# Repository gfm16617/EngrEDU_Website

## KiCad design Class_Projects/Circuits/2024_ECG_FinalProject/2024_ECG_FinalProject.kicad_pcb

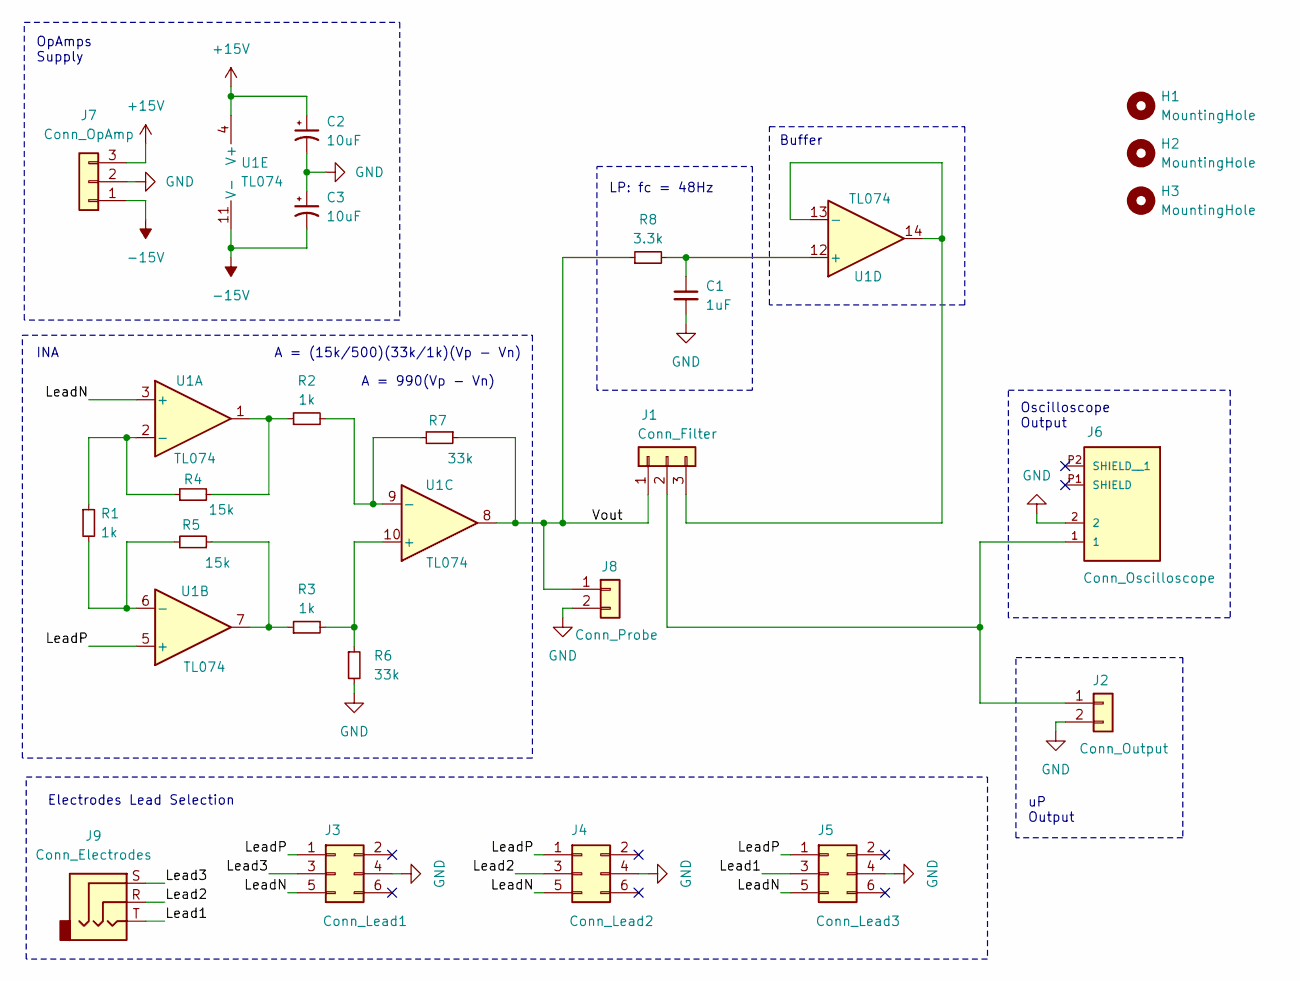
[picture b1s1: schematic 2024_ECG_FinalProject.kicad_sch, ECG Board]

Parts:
C1: 1uF; C_Disc_D5.0mm_W2.5mm_P5.00mm
C2, C3: 10uF; CP_Radial_D5.0mm_P2.50mm
H1, H2, H3: MountingHole; MountingHole_3.2mm_M3_Pad
J1: Conn_Filter; PinHeader_1x03_P2.54mm_Vertical
J2: Conn_Output; PinHeader_1x02_P2.54mm_Vertical
J3: Conn_Lead1; PinHeader_2x03_P2.54mm_Vertical
J4: Conn_Lead2; PinHeader_2x03_P2.54mm_Vertical
J5: Conn_Lead3; PinHeader_2x03_P2.54mm_Vertical
J6: Conn_Oscilloscope; BNC_RightAngle_50ohm
J7: Conn_OpAmp; PinHeader_1x03_P2.54mm_Vertical
J8: Conn_Probe; PinHeader_1x02_P2.54mm_Vertical
J9: Conn_Electrodes; AudioJack_CUI_3mm5
R1, R2, R3: 1k; R_Axial_DIN0207_L6.3mm_D2.5mm_P10.16mm_Horizontal
R4, R5: 15k; R_Axial_DIN0207_L6.3mm_D2.5mm_P10.16mm_Horizontal
R6, R7: 33k; R_Axial_DIN0207_L6.3mm_D2.5mm_P10.16mm_Horizontal
R8: 3.3k; R_Axial_DIN0207_L6.3mm_D2.5mm_P10.16mm_Horizontal
U1: TL074; CERDIP-14_W7.62mm_SideBrazed_LongPads_Socket

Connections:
+15V: C2.1, J7.3, U1.4 (V+)
-15V: C3.2, J7.1, U1.11 (V-)
/Lead1: J5.3, J9.T
/Lead2: J4.3, J9.R
/Lead3: J3.3, J9.S
/LeadN: J3.5, J4.5, J5.5, U1.3 (+)
/LeadP: J3.1, J4.1, J5.1, U1.5 (+)
/Vout: J1.1, J8.1, R7.1, R8.1, U1.8
GND: C1.2, C2.2, C3.1, J2.2, J3.4, J4.4, J5.4, J6.2, J7.2, J8.2, R6.2
unnamed: J1.2, J2.1, J6.1
unnamed: J1.3, U1.13 (-), U1.14
unnamed: R2.1, R4.2, U1.1
unnamed: R3.1, R5.2, U1.7
unnamed: R1.1, R4.1, U1.2 (-)
unnamed: R1.2, R5.1, U1.6 (-)
unnamed: R3.2, R6.1, U1.10 (+)
unnamed: R2.2, R7.2, U1.9 (-)
unnamed: C1.1, R8.2, U1.12 (+)

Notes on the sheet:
INA
Buffer
A = 990(Vp - Vn)
OpAmps Supply
Oscilloscope Output
A = (15k/500)(33k/1k)(Vp - Vn)
uP Output
Electrodes Lead Selection
LP: fc = 48Hz

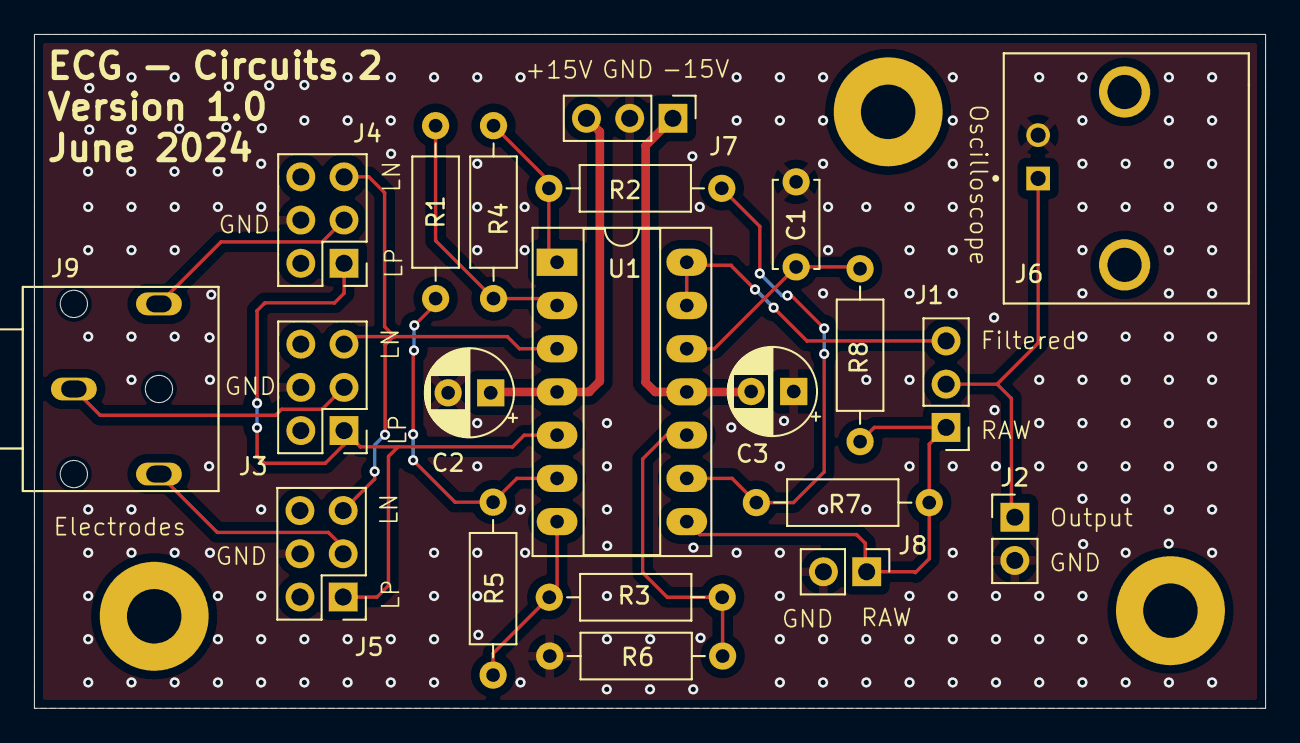
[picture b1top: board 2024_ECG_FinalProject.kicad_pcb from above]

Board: 2 copper layers, 72.3 x 39.6 mm, 24 parts (0 on the bottom side), 18 nets.

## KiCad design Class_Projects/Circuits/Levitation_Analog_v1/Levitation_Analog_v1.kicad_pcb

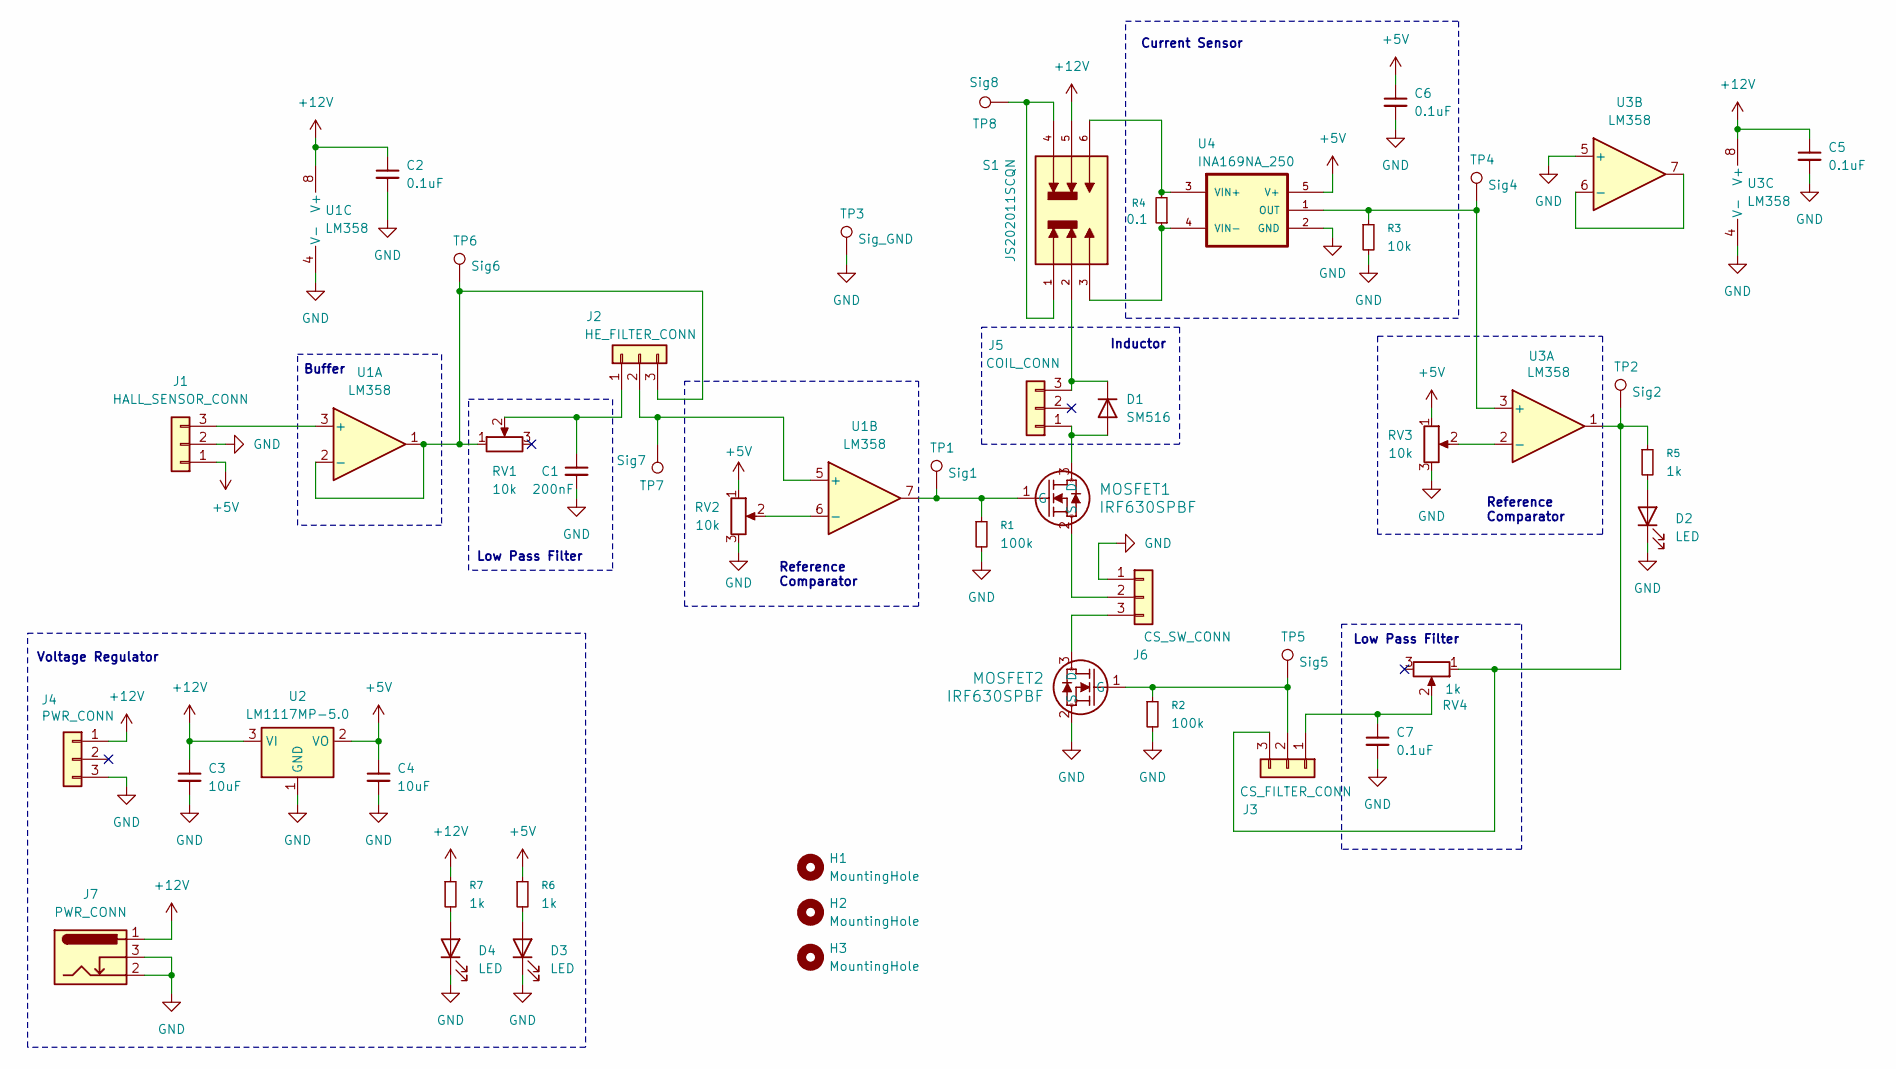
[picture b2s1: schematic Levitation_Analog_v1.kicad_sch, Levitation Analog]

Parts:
C1: 200nF; C_1206_3216Metric_Pad1.33x1.80mm_HandSolder; Mfr. # 12065C204KAT4A
C2, C5, C6, C7: 0.1uF; C_1206_3216Metric_Pad1.33x1.80mm_HandSolder; Mfr. # KAM31NR72A104KU
C3, C4: 10uF; C_1206_3216Metric_Pad1.33x1.80mm_HandSolder; Mfr. # GXT31CR6YA106KE01L
D1: SM516; D_MELF; Mfr. # SM516
D2, D3, D4: LED; LED_1206_3216Metric; Mfr. # HSMG-C150
H1, H2, H3: MountingHole; MountingHole_3.2mm_M3_Pad
J1: HALL_SENSOR_CONN; JST_XA_B03B-XASK-1_1x03_P2.50mm_Vertical
J2: HE_FILTER_CONN; PinHeader_1x03_P2.54mm_Vertical
J3: CS_FILTER_CONN; PinHeader_1x03_P2.54mm_Vertical
J4: PWR_CONN; JST_XA_B03B-XASK-1_1x03_P2.50mm_Vertical
J5: COIL_CONN; JST_XA_B03B-XASK-1_1x03_P2.50mm_Vertical
J6: CS_SW_CONN; PinHeader_1x03_P2.54mm_Vertical
J7: PWR_CONN; BarrelJack_Horizontal
MOSFET1, MOSFET2: IRF630SPBF; TO-263AB_HIGHVOLTAGE-M; Mfr. # IRF630SPBF
R1, R2: 100k; R_1206_3216Metric_Pad1.30x1.75mm_HandSolder; Mfr. # RVCU1206FT100K
R3: 10k; R_1206_3216Metric_Pad1.30x1.75mm_HandSolder; Mfr. # SFR18EZPJ103
R4: 0.1; R_1206_3216Metric_Pad1.30x1.75mm_HandSolder; Mfr. # TLMQ2BDR10FTD
R5, R6, R7: 1k; R_1206_3216Metric_Pad1.30x1.75mm_HandSolder; Mfr. # RK73H2BLTD1001F
RV1, RV2, RV3: 10k; Potentiometer_Alps_RK09K_Single_Vertical
RV4: 1k; Potentiometer_Alps_RK09K_Single_Vertical
S1: JS202011SCQN; SW_JS202011SCQN; PARTREV 26 May 22
TP1: Sig1; TestPoint_Loop_D2.50mm_Drill1.0mm
TP2: Sig2; TestPoint_Loop_D2.50mm_Drill1.0mm
TP3: Sig_GND; TestPoint_Loop_D2.50mm_Drill1.0mm
TP4: Sig4; TestPoint_Loop_D2.50mm_Drill1.0mm
TP5: Sig5; TestPoint_Loop_D2.50mm_Drill1.0mm
TP6: Sig6; TestPoint_Loop_D2.50mm_Drill1.0mm
TP7: Sig7; TestPoint_Loop_D2.50mm_Drill1.0mm
TP8: Sig8; TestPoint_Loop_D2.50mm_Drill1.0mm
U1, U3: LM358; SOP-8_3.76x4.96mm_P1.27mm; Mfr. # LM358F-GE2
U2: LM1117MP-5.0; SOT-223-3_TabPin2; Mfr. # LM1117MPX-50NOPB
U4: INA169NA_250; SOT95P280X145-5N; Mfr. # INA169NA/3K

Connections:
+5V: C4.1, C6.1, J1.1, R6.1, RV2.1, RV3.1, U2.2 (VO), U4.5 (V+)
+12V: C2.1, C3.1, C5.1, J4.1, J7.1, R7.1, S1.5, U1.8 (V+), U2.3 (VI), U3.8 (V+)
GND: C1.2, C2.2, C3.2, C4.2, C5.2, C6.2, C7.2, D2.1 (K), D3.1 (K), D4.1 (K), J1.2, J4.3, J6.1, J7.2, J7.3, MOSFET2.2 (S), R1.2, R2.2, R3.2, RV2.3, RV3.3, TP3.1, U1.4 (V-), U2.1 (GND), U3.4 (V-), U3.5 (+), U4.2 (GND)
unnamed: D1.2 (A), J5.1, MOSFET1.3 (D)
unnamed: D1.1 (K), J5.3, S1.2
unnamed: D2.2 (A), R5.2
unnamed: D3.2 (A), R6.2
unnamed: D4.2 (A), R7.2
unnamed: J1.3, U1.3 (+)
unnamed: C1.1, J2.1, RV1.2
unnamed: J2.2, TP7.1, U1.5 (+)
unnamed: J2.3, RV1.1, TP6.1, U1.1, U1.2 (-)
unnamed: C7.1, J3.1, RV4.2
unnamed: J3.2, MOSFET2.1 (G), R2.1, TP5.1
unnamed: J3.3, R5.1, RV4.1, TP2.1, U3.1
unnamed: J6.2, MOSFET1.2 (S)
unnamed: J6.3, MOSFET2.3 (D)
unnamed: MOSFET1.1 (G), R1.1, TP1.1, U1.7
unnamed: S1.1, S1.4, TP8.1
unnamed: RV2.2, U1.6 (-)
unnamed: R3.1, TP4.1, U3.3 (+), U4.1 (OUT)
unnamed: RV3.2, U3.2 (-)
unnamed: U3.6 (-), U3.7
unnamed: R4.2, S1.6, U4.3 (VIN+)
unnamed: R4.1, S1.3, U4.4 (VIN-)

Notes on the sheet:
Reference Comparator
Low Pass Filter
Current Sensor
Inductor
Buffer
Voltage Regulator

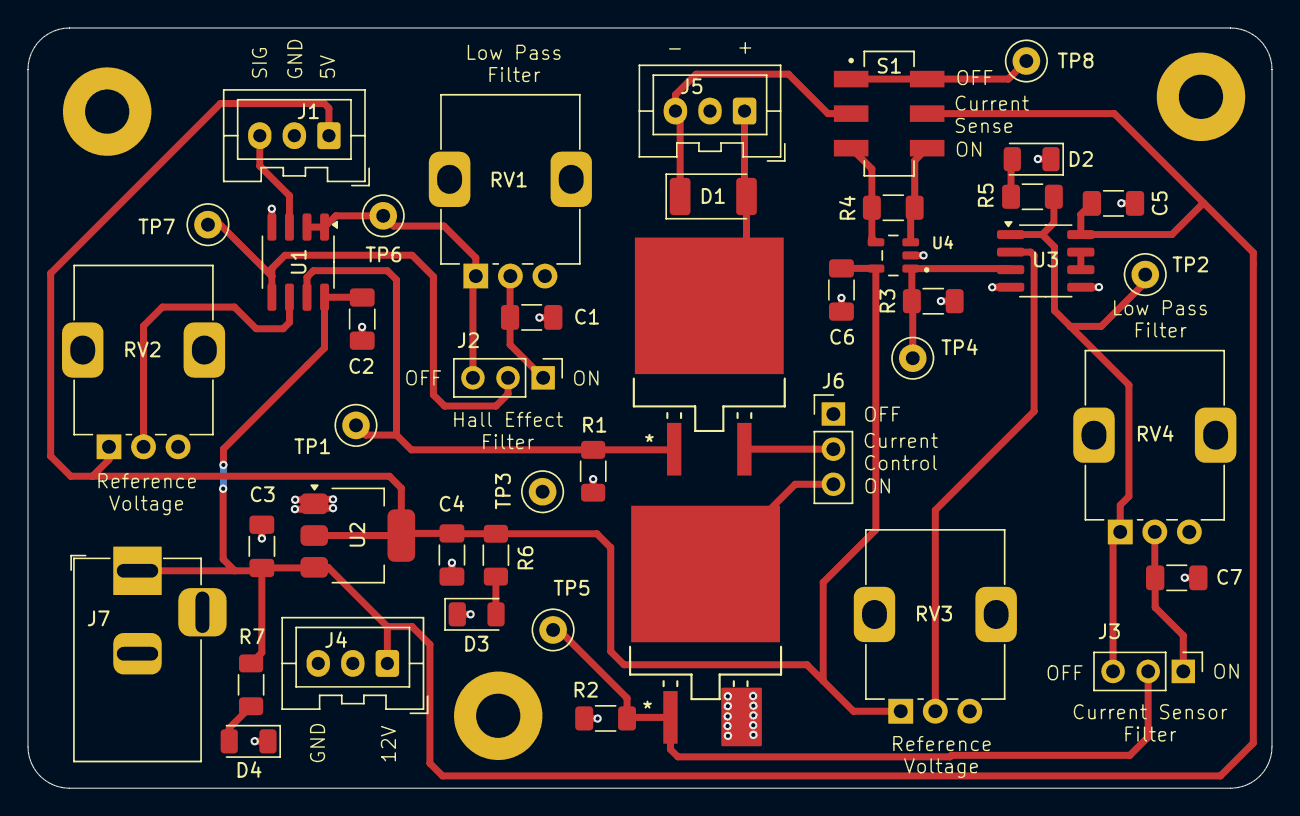
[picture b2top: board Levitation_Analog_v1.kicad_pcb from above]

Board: 2 copper layers, 90.0 x 55.0 mm, 47 parts (0 on the bottom side), 25 nets.

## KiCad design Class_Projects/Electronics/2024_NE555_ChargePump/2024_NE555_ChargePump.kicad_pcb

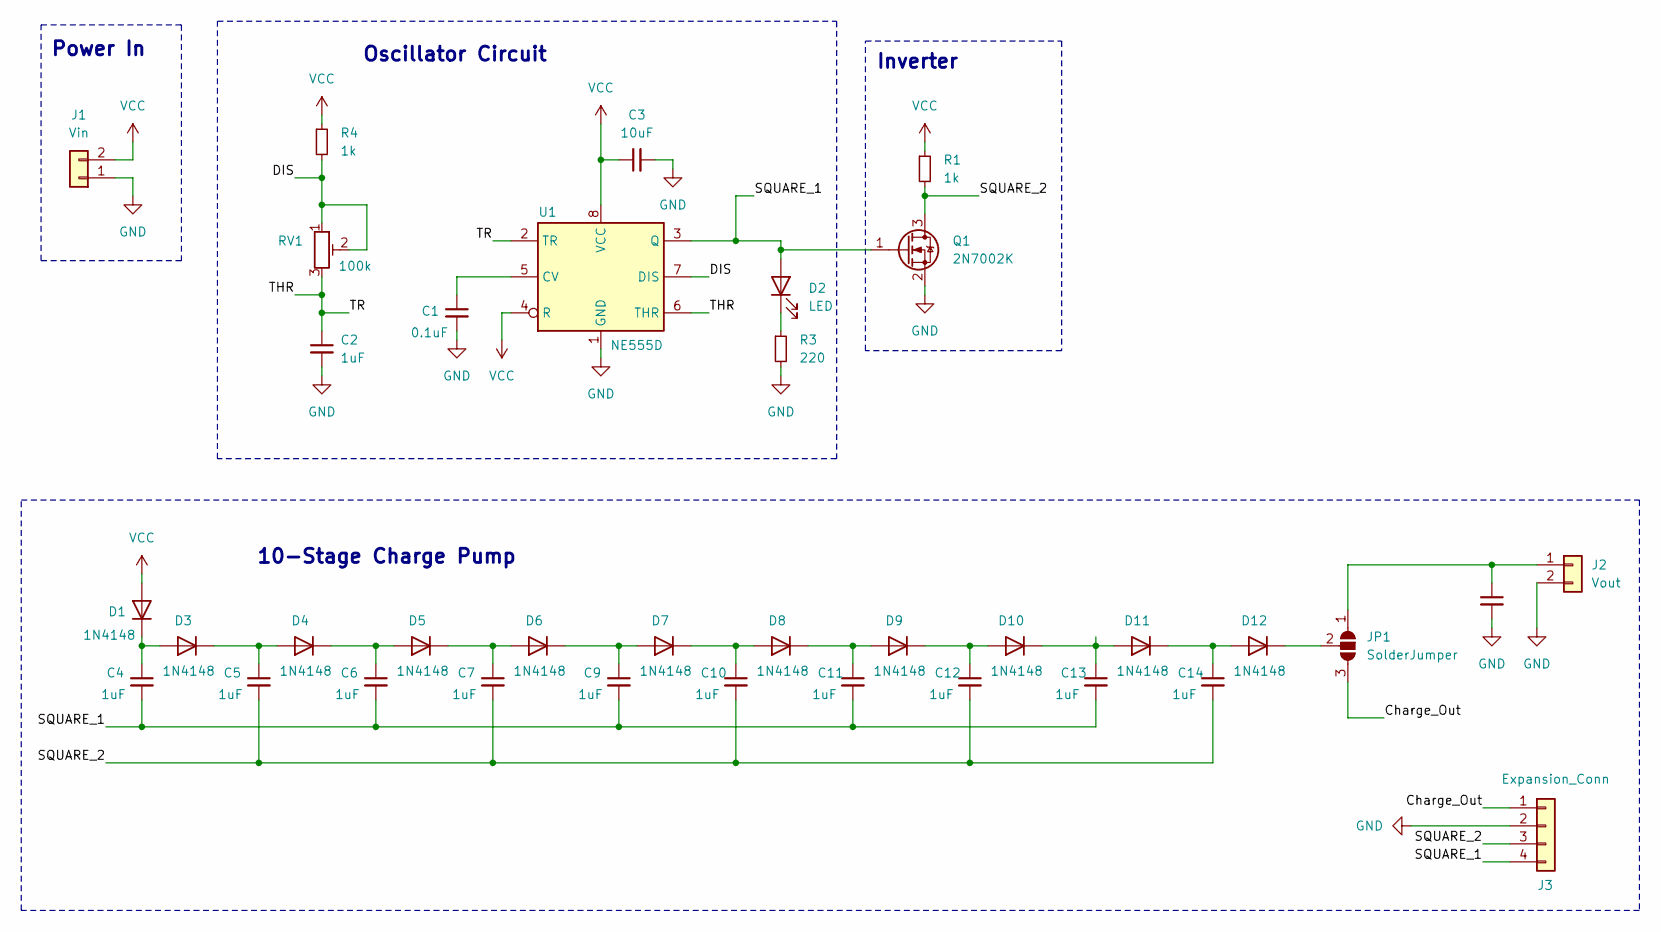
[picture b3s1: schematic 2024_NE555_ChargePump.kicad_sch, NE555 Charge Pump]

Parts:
C1: 0.1uF; C_0805_2012Metric_Pad1.18x1.45mm_HandSolder
C2: 1uF; C_0805_2012Metric_Pad1.18x1.45mm_HandSolder
C3: 10uF; C_1206_3216Metric_Pad1.33x1.80mm_HandSolder
C4, C5, C6, C7, C8, C9, C10, C11, C12, C13, C14: 1uF; C_1206_3216Metric_Pad1.33x1.80mm_HandSolder
D1, D3, D4, D5, D6, D7, D8, D9, D10, D11, D12: 1N4148; D_MicroMELF_Handsoldering
D2: LED; LED_1206_3216Metric_Pad1.42x1.75mm_HandSolder
J1: Vin; TerminalBlock_bornier-2_P5.08mm
J2: Vout; PinHeader_1x02_P2.54mm_Vertical
J3: Expansion_Conn; PinHeader_1x04_P2.54mm_Horizontal
JP1: SolderJumper; SolderJumper-3_P1.3mm_Open_RoundedPad1.0x1.5mm
Q1: 2N7002K; SOT-23
R1, R4: 1k; R_0805_2012Metric_Pad1.20x1.40mm_HandSolder
R3: 220; R_0805_2012Metric_Pad1.20x1.40mm_HandSolder
RV1: 100k; Trim_Pot_100k
U1: NE555D; SOIC-8_3.9x4.9mm_P1.27mm

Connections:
/Charge_Out: J3.1, JP1.3 (B)
/DIS: R4.2, RV1.1, RV1.2, U1.7 (DIS)
/SQUARE_1: C4.2, C6.2, C9.2, C11.2, C13.2, D2.2 (A), J3.4, Q1.1 (G), U1.3 (Q)
/SQUARE_2: C5.2, C7.2, C10.2, C12.2, C14.2, J3.3, Q1.3 (D), R1.2
/THR: C2.1, RV1.3, U1.2 (TR), U1.6 (THR)
GND: C1.2, C2.2, C3.2, C8.2, J1.1, J2.2, J3.2, Q1.2 (S), R3.2, U1.1 (GND)
unnamed: C4.1, D1.1 (K), D3.2 (A)
unnamed: D2.1 (K), R3.1
unnamed: C5.1, D3.1 (K), D4.2 (A)
unnamed: C6.1, D4.1 (K), D5.2 (A)
unnamed: C7.1, D5.1 (K), D6.2 (A)
unnamed: C9.1, D6.1 (K), D7.2 (A)
unnamed: C10.1, D7.1 (K), D8.2 (A)
unnamed: C11.1, D8.1 (K), D9.2 (A)
unnamed: C12.1, D9.1 (K), D10.2 (A)
unnamed: C13.1, D10.1 (K), D11.2 (A)
unnamed: C14.1, D11.1 (K), D12.2 (A)
unnamed: D12.1 (K), JP1.2 (C)
unnamed: C8.1, J2.1, JP1.1 (A)
unnamed: C1.1, U1.5 (CV)
VCC: C3.1, D1.2 (A), J1.2, R1.1, R4.1, U1.4 (R), U1.8 (VCC)

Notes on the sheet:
Power In
Inverter
10-Stage Charge Pump
Oscillator Circuit

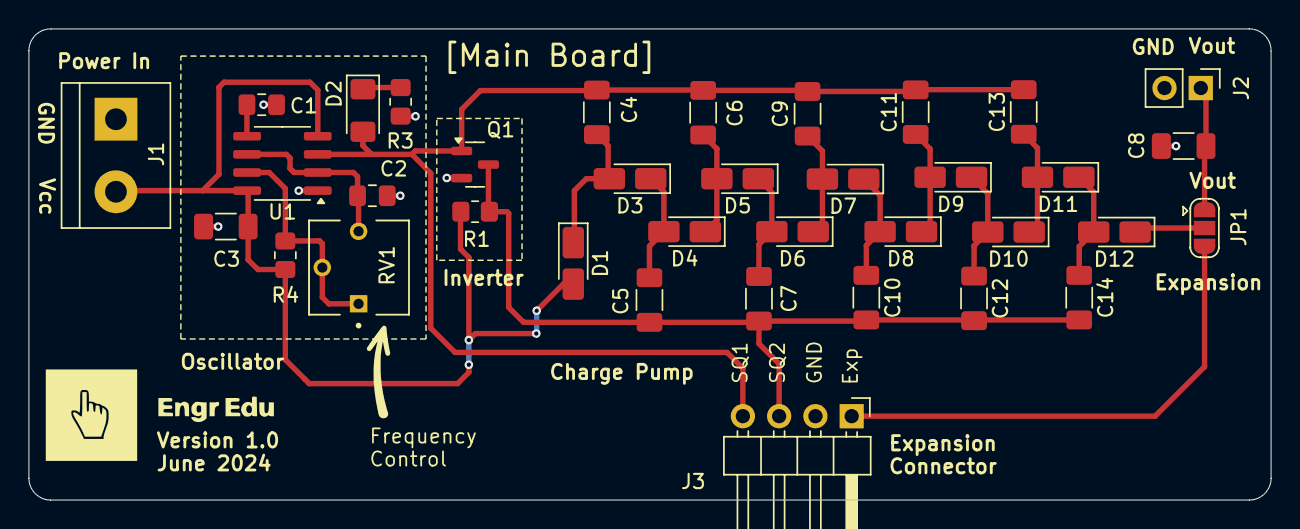
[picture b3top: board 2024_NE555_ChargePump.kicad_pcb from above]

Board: 2 copper layers, 87.0 x 33.0 mm, 36 parts (0 on the bottom side), 21 nets.

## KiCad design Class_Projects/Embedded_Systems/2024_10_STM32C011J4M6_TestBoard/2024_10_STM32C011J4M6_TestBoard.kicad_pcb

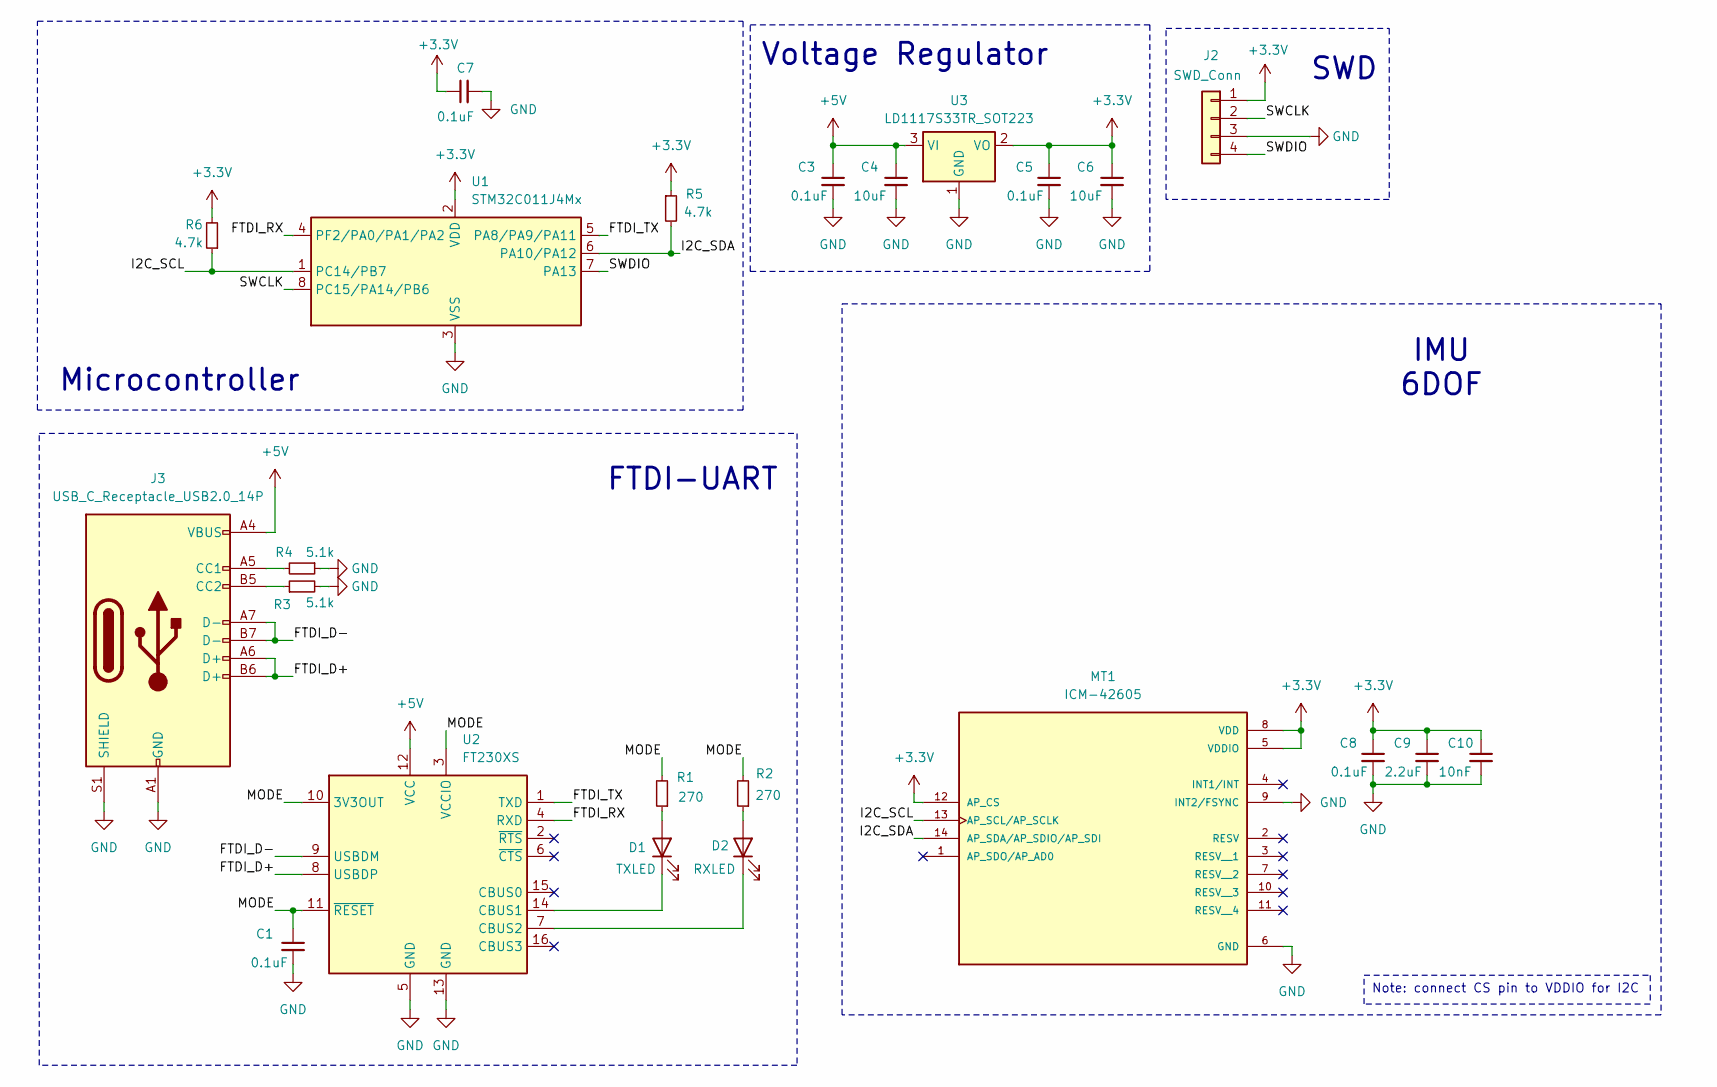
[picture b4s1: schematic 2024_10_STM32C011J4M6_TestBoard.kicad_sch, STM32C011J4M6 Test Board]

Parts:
C1, C3, C5, C7, C8: 0.1uF; C_0603_1608Metric_Pad1.08x0.95mm_HandSolder; Mfg Part# CC0603JRX7R9BB104
C4, C6: 10uF; C_0603_1608Metric_Pad1.08x0.95mm_HandSolder; Mfg Part# MSASL168BB5106KTNB33
C9: 2.2uF; C_0603_1608Metric_Pad1.08x0.95mm_HandSolder; Mfg Part# MBASL168SB5225KTNA01
C10: 10nF; C_0603_1608Metric_Pad1.08x0.95mm_HandSolder; Mfg Part# AS0603KRX7R0BB103
D1: TXLED; LED_0603_1608Metric_Pad1.05x0.95mm_HandSolder; Mfg Part# 150060YS75000
D2: RXLED; LED_0603_1608Metric_Pad1.05x0.95mm_HandSolder; Mfg Part# 150060VS75000
J2: SWD_Conn; JST_SH_BM04B-SRSS-TB_1x04-1MP_P1.00mm_Vertical
J3: USB_C_Receptacle_USB2.0_14P; USB_C_Receptacle_HCTL_HC-TYPE-C-16P-01A; Mfg Part# UJ20-C-H-C-4-SMT-TR
MT1: ICM-42605; ICM_42605; PARTREV 1.7
R1, R2: 270; R_0603_1608Metric_Pad0.98x0.95mm_HandSolder; Mfg Part# CRCW0603270RFKTA
R3, R4: 5.1k; R_0603_1608Metric_Pad0.98x0.95mm_HandSolder; Mfg Part# CRCW06035K10FKEC
R5, R6: 4.7k; R_0603_1608Metric_Pad0.98x0.95mm_HandSolder; Mfg Part# RMC1/16K4701FTP
U1: STM32C011J4Mx; SOIC-8_3.9x4.9mm_P1.27mm; Mfg Part# STM32C011J4M6
U2: FT230XS; SSOP-16_3.9x4.9mm_P0.635mm; Mfg Part# FT230XS-U
U3: LD1117S33TR_SOT223; SOT-223-3_TabPin2; Mfg Part# LD1117S33TR

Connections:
+3.3V: C5.1, C6.1, C7.1, C8.1, C9.1, C10.1, J2.1, MT1.5 (VDDIO), MT1.8 (VDD), MT1.12 (AP_CS), R5.1, R6.2, U1.2 (VDD), U3.2 (VO)
+5V: C3.1, C4.1, J3.A4 (VBUS), J3.A9 (VBUS), J3.B4 (VBUS), J3.B9 (VBUS), U2.12 (VCC), U3.3 (VI)
/FTDI_D+: J3.A6 (D+), J3.B6 (D+), U2.8 (USBDP)
/FTDI_D-: J3.A7 (D-), J3.B7 (D-), U2.9 (USBDM)
/FTDI_RX: U1.4 (PF2/PA0/PA1/PA2), U2.4 (RXD)
/FTDI_TX: U1.5 (PA8/PA9/PA11), U2.1 (TXD)
/I2C_SCL: MT1.13 (AP_SCL/AP_SCLK), R6.1, U1.1 (PC14/PB7)
/I2C_SDA: MT1.14 (AP_SDA/AP_SDIO/AP_SDI), R5.2, U1.6 (PA10/PA12)
/MODE: C1.1, R1.2, R2.2, U2.3 (VCCIO), U2.10 (3V3OUT), U2.11 (~RESET)
/SWCLK: J2.2, U1.8 (PC15/PA14/PB6)
/SWDIO: J2.4, U1.7 (PA13)
GND: C1.2, C3.2, C4.2, C5.2, C6.2, C7.2, C8.2, C9.2, C10.2, J2.3, J3.A1 (GND), J3.A12 (GND), J3.B1 (GND), J3.B12 (GND), J3.S1 (SHIELD), MT1.6 (GND), MT1.9 (INT2/FSYNC), R3.2, R4.1, U1.3 (VSS), U2.5 (GND), U2.13 (GND), U3.1 (GND)
unnamed: D1.2 (A), R1.1
unnamed: D1.1 (K), U2.14 (CBUS1)
unnamed: D2.2 (A), R2.1
unnamed: D2.1 (K), U2.7 (CBUS2)
unnamed: J3.A5 (CC1), R4.2
unnamed: J3.B5 (CC2), R3.1

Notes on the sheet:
Note: connect CS pin to VDDIO for I2C
Voltage Regulator
Microcontroller
SWD
IMU 6DOF
FTDI-UART

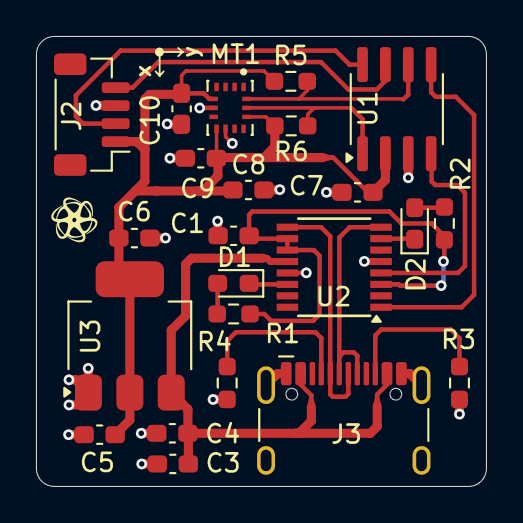
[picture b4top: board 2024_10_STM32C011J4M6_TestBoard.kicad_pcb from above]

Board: 2 copper layers, 25.0 x 25.0 mm, 23 parts (0 on the bottom side), 18 nets.

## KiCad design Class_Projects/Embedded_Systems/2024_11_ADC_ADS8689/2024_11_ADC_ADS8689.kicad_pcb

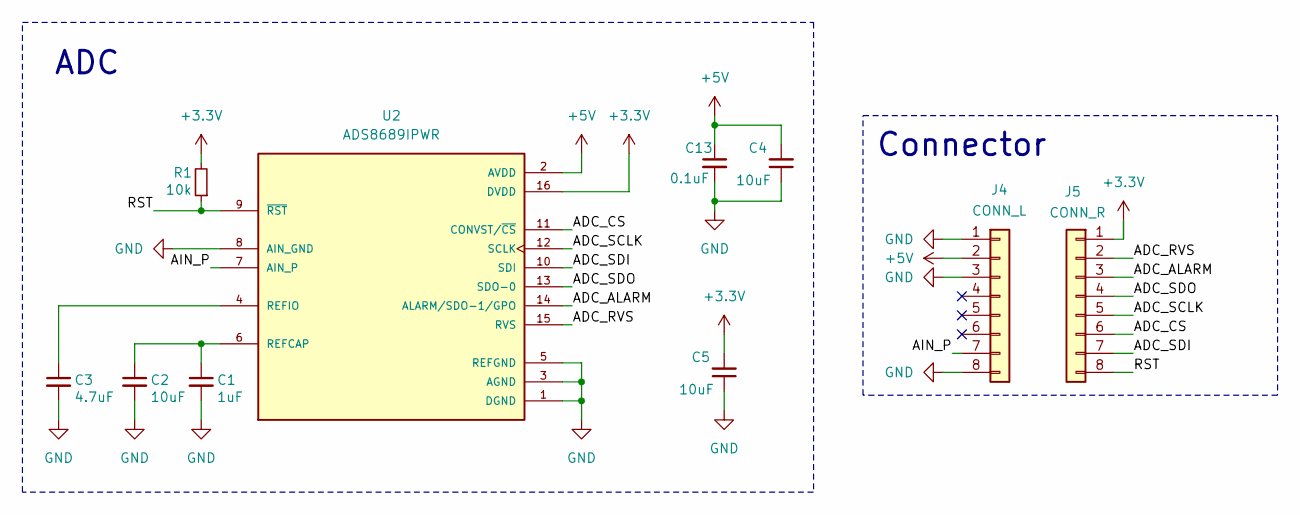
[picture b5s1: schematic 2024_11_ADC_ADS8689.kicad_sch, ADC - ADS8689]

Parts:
C1: 1uF; C_0805_2012Metric_Pad1.18x1.45mm_HandSolder; Mfg Part# KGM21AR51E105KU
C2, C4, C5: 10uF; C_0805_2012Metric_Pad1.18x1.45mm_HandSolder; Mfg Part# CL21B106KOYNNWE
C3: 4.7uF; C_0805_2012Metric_Pad1.18x1.45mm_HandSolder; Mfg Part# LMK212BJ475KG-T
C13: 0.1uF; C_0805_2012Metric_Pad1.18x1.45mm_HandSolder; Mfg Part# C0805C104K4JACAUTO
J4: CONN_L; PinHeader_1x08_P2.54mm_Vertical
J5: CONN_R; PinHeader_1x08_P2.54mm_Vertical
R1: 10k; R_0805_2012Metric; Mfg Part# RK73B2ATTE103J
U2: ADS8689IPWR; ADS8689; PARTREV D

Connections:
+3.3V: C5.2, J5.1, R1.2, U2.16 (DVDD)
+5V: C4.2, C13.1, J4.2, U2.2 (AVDD)
/ADC_ALARM: J5.3, U2.14 (ALARM/SDO-1/GPO)
/ADC_CS: J5.6, U2.11 (CONVST/~CS)
/ADC_RVS: J5.2, U2.15 (RVS)
/ADC_SCLK: J5.5, U2.12 (SCLK)
/ADC_SDI: J5.7, U2.10 (SDI)
/ADC_SDO: J5.4, U2.13 (SDO-0)
/AIN_P: J4.7, U2.7 (AIN_P)
/RST: J5.8, R1.1, U2.9 (~RST)
GND: C1.2, C2.2, C3.2, C4.1, C5.1, C13.2, J4.1, J4.3, J4.8, U2.1 (DGND), U2.3 (AGND), U2.5 (REFGND), U2.8 (AIN_GND)
unnamed: C1.1, C2.1, U2.6 (REFCAP)
unnamed: C3.1, U2.4 (REFIO)

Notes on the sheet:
ADC
Connector

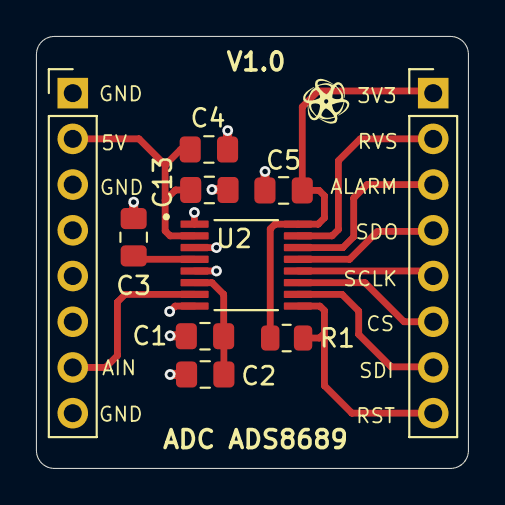
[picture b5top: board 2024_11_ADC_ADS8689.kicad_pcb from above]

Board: 2 copper layers, 24.0 x 24.0 mm, 10 parts (0 on the bottom side), 13 nets.

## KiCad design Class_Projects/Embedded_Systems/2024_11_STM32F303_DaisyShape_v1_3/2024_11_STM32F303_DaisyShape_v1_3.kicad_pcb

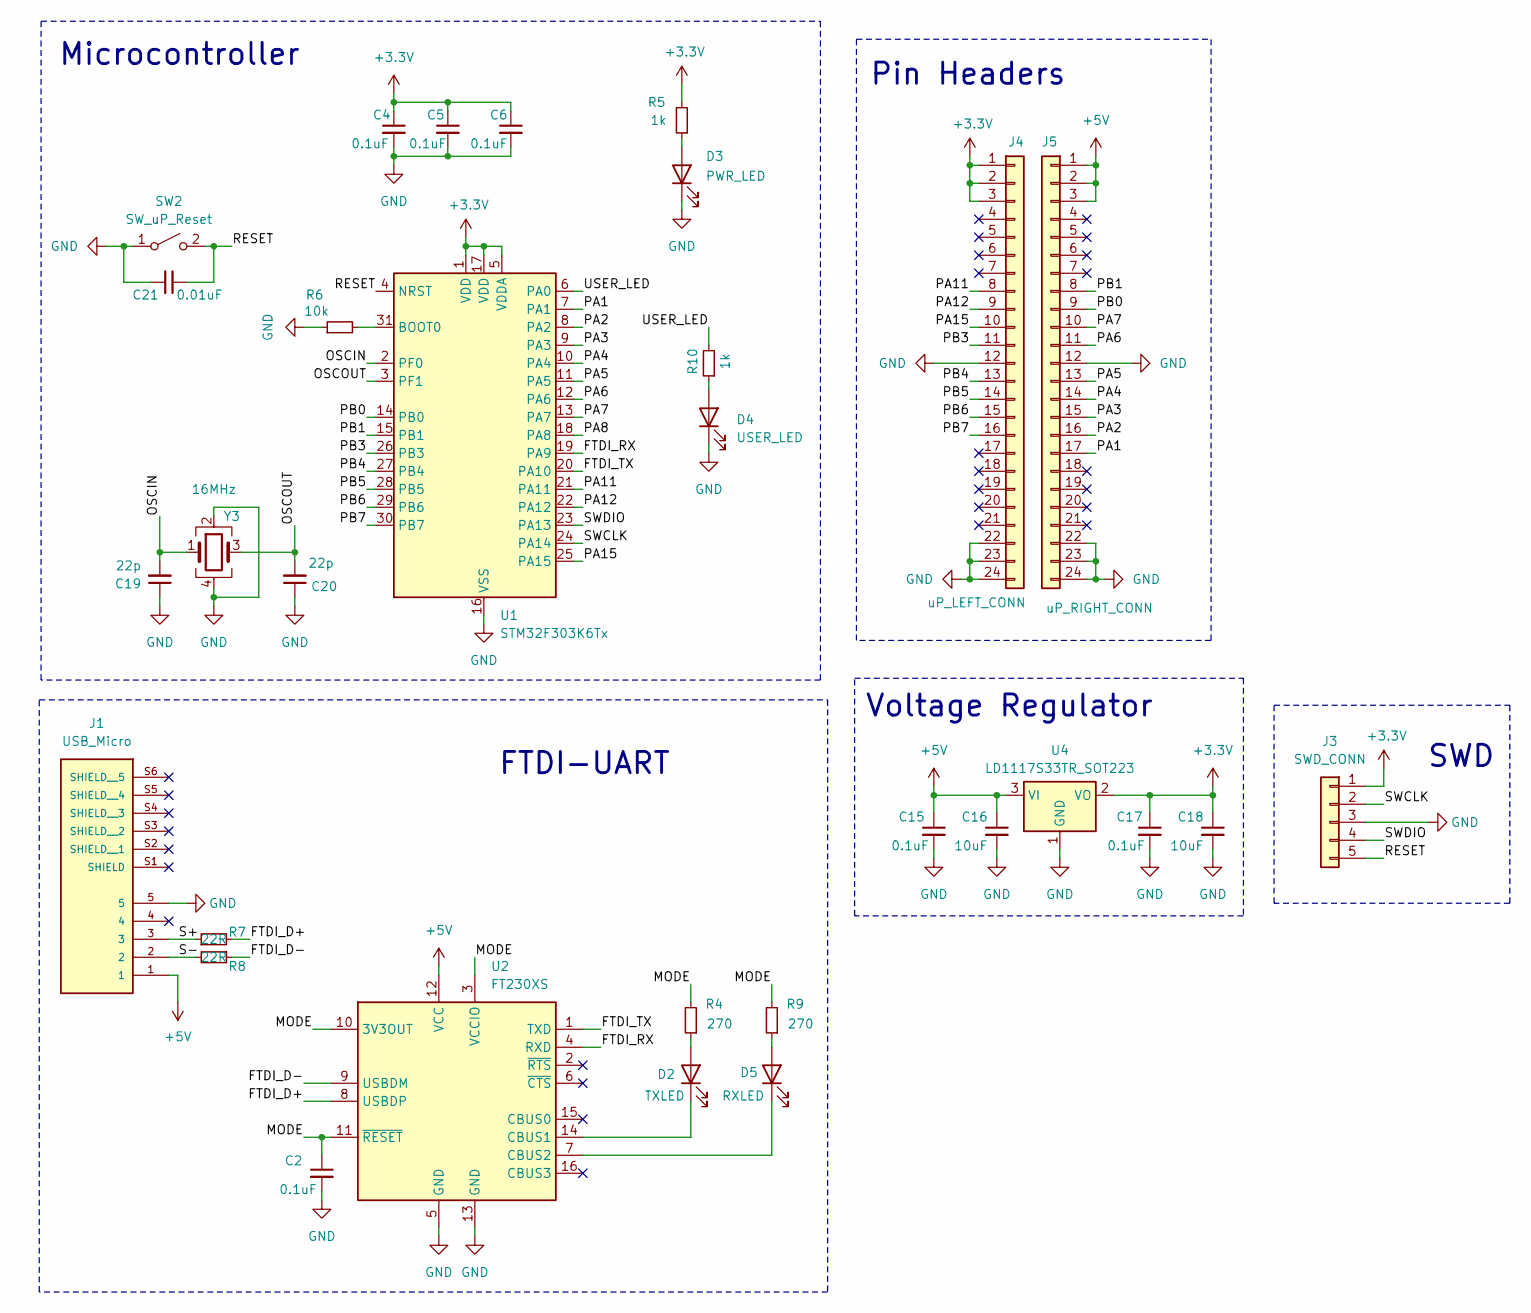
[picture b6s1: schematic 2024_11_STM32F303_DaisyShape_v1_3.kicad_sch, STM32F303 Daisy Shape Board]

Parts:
C2, C4, C5, C6, C15, C17: 0.1uF; C_0805_2012Metric_Pad1.18x1.45mm_HandSolder; Mfg Part# C0805C104K4JACAUTO
C16, C18: 10uF; C_0805_2012Metric_Pad1.18x1.45mm_HandSolder; Mfg Part# C0805C106K4PACTU
C19, C20: 22p; C_0805_2012Metric_Pad1.18x1.45mm_HandSolder; Mfg Part# 08055C220KAT2A
C21: 0.01uF; C_0805_2012Metric_Pad1.18x1.45mm_HandSolder; Mfg Part# KAF21BR72A103JT
D2: TXLED; LED_0805_2012Metric_Pad1.15x1.40mm_HandSolder; Mfg Part# 150080VS75000
D3: PWR_LED; LED_0805_2012Metric_Pad1.15x1.40mm_HandSolder; Mfg Part# 150080RS75000
D4: USER_LED; LED_0805_2012Metric_Pad1.15x1.40mm_HandSolder; Mfg Part# 150080BS75000
D5: RXLED; LED_0805_2012Metric_Pad1.15x1.40mm_HandSolder; Mfg Part# 150080BS75000
J1: USB_Micro; AMPHENOL_10118194-0001LF; PARTREV D
J3: SWD_CONN; JST_SH_BM05B-SRSS-TB_1x05-1MP_P1.00mm_Vertical
J4: uP_LEFT_CONN; PinHeader_1x24_P2.54mm_Vertical
J5: uP_RIGHT_CONN; PinHeader_1x24_P2.54mm_Vertical
R4, R9: 270; R_0805_2012Metric_Pad1.20x1.40mm_HandSolder; Mfg Part# CRGCQ0805F270R
R5, R10: 1k; R_0805_2012Metric_Pad1.20x1.40mm_HandSolder; Mfg Part# TNPW08051K00FEEA
R6: 10k; R_0805_2012Metric_Pad1.20x1.40mm_HandSolder; Mfg Part# CPF0805B10KE1
R7, R8: 22R; R_0805_2012Metric_Pad1.20x1.40mm_HandSolder; Mfg Part# RCA080522R0FKEA
SW2: SW_uP_Reset; Mfg Part# 434121025816
U1: STM32F303K6Tx; LQFP-32_7x7mm_P0.8mm; Mfg Part# STM32F303K6T6
U2: FT230XS; SSOP-16_3.9x4.9mm_P0.635mm; Mfg Part# FT230XS-U
U4: LD1117S33TR_SOT223; SOT-223-3_TabPin2; Mfg Part# LD1117S33TR
Y3: 16MHz; Crystal_SMD_Abracon_ABM8G-4Pin_3.2x2.5mm; Mfg Part# ABM8-16.000MHZ-D1X-T

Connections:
+3.3V: C4.1, C5.1, C6.1, C17.1, C18.1, J3.1, J4.1, J4.2, J4.3, R5.2, U1.1 (VDD), U1.5 (VDDA), U1.17 (VDD), U4.2 (VO)
+5V: C15.1, C16.1, J1.1, J5.1, J5.2, J5.3, U2.12 (VCC), U4.3 (VI)
/FTDI_D+: R7.2, U2.8 (USBDP)
/FTDI_D-: R8.1, U2.9 (USBDM)
/FTDI_RX: U1.19 (PA9), U2.4 (RXD)
/FTDI_TX: U1.20 (PA10), U2.1 (TXD)
/MODE: C2.1, R4.2, R9.2, U2.3 (VCCIO), U2.10 (3V3OUT), U2.11 (~RESET)
/OSCIN: C19.2, U1.2 (PF0), Y3.1
/OSCOUT: C20.2, U1.3 (PF1), Y3.3
/PA1: J5.17, U1.7 (PA1)
/PA2: J5.16, U1.8 (PA2)
/PA3: J5.15, U1.9 (PA3)
/PA4: J5.14, U1.10 (PA4)
/PA5: J5.13, U1.11 (PA5)
/PA6: J5.11, U1.12 (PA6)
/PA7: J5.10, U1.13 (PA7)
/PA8: U1.18 (PA8)
/PA11: J4.8, U1.21 (PA11)
/PA12: J4.9, U1.22 (PA12)
/PA15: J4.10, U1.25 (PA15)
/PB0: J5.9, U1.14 (PB0)
/PB1: J5.8, U1.15 (PB1)
/PB3: J4.11, U1.26 (PB3)
/PB4: J4.13, U1.27 (PB4)
/PB5: J4.14, U1.28 (PB5)
/PB6: J4.15, U1.29 (PB6)
/PB7: J4.16, U1.30 (PB7)
/RESET: C21.1, J3.5, SW2.2 (B), U1.4 (NRST)
/S+: J1.3, R7.1
/S-: J1.2, R8.2
/SWCLK: J3.2, U1.24 (PA14)
/SWDIO: J3.4, U1.23 (PA13)
/USER_LED: R10.2, U1.6 (PA0)
GND: C2.2, C4.2, C5.2, C6.2, C15.2, C16.2, C17.2, C18.2, C19.1, C20.1, C21.2, D3.1 (K), D4.1 (K), J1.5, J3.3, J4.12, J4.22, J4.23, J4.24, J5.12, J5.22, J5.23, J5.24, R6.1, SW2.1 (A), U1.16 (VSS), U1.32 (VSS), U2.5 (GND), U2.13 (GND), U4.1 (GND), Y3.2, Y3.4
unnamed: D2.2 (A), R4.1
unnamed: D2.1 (K), U2.14 (CBUS1)
unnamed: D3.2 (A), R5.1
unnamed: D4.2 (A), R10.1
unnamed: D5.2 (A), R9.1
unnamed: D5.1 (K), U2.7 (CBUS2)
unnamed: R6.2, U1.31 (BOOT0)

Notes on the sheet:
SWD
Voltage Regulator
Microcontroller
FTDI-UART
Pin Headers

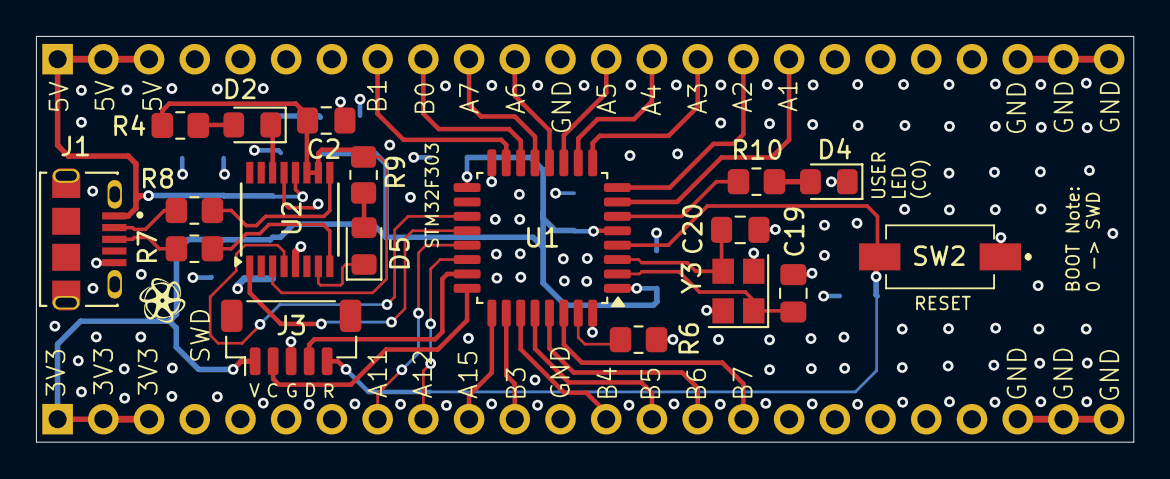
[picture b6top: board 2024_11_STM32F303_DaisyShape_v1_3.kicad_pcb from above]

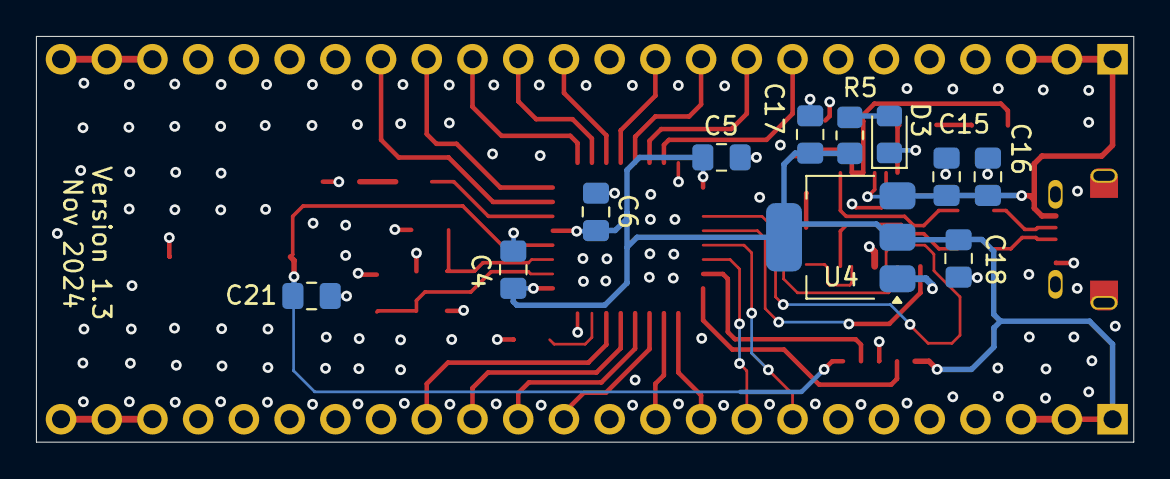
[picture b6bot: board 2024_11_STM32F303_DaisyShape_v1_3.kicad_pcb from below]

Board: 4 copper layers, 61.0 x 22.5 mm, 31 parts (11 on the bottom side), 40 nets.
